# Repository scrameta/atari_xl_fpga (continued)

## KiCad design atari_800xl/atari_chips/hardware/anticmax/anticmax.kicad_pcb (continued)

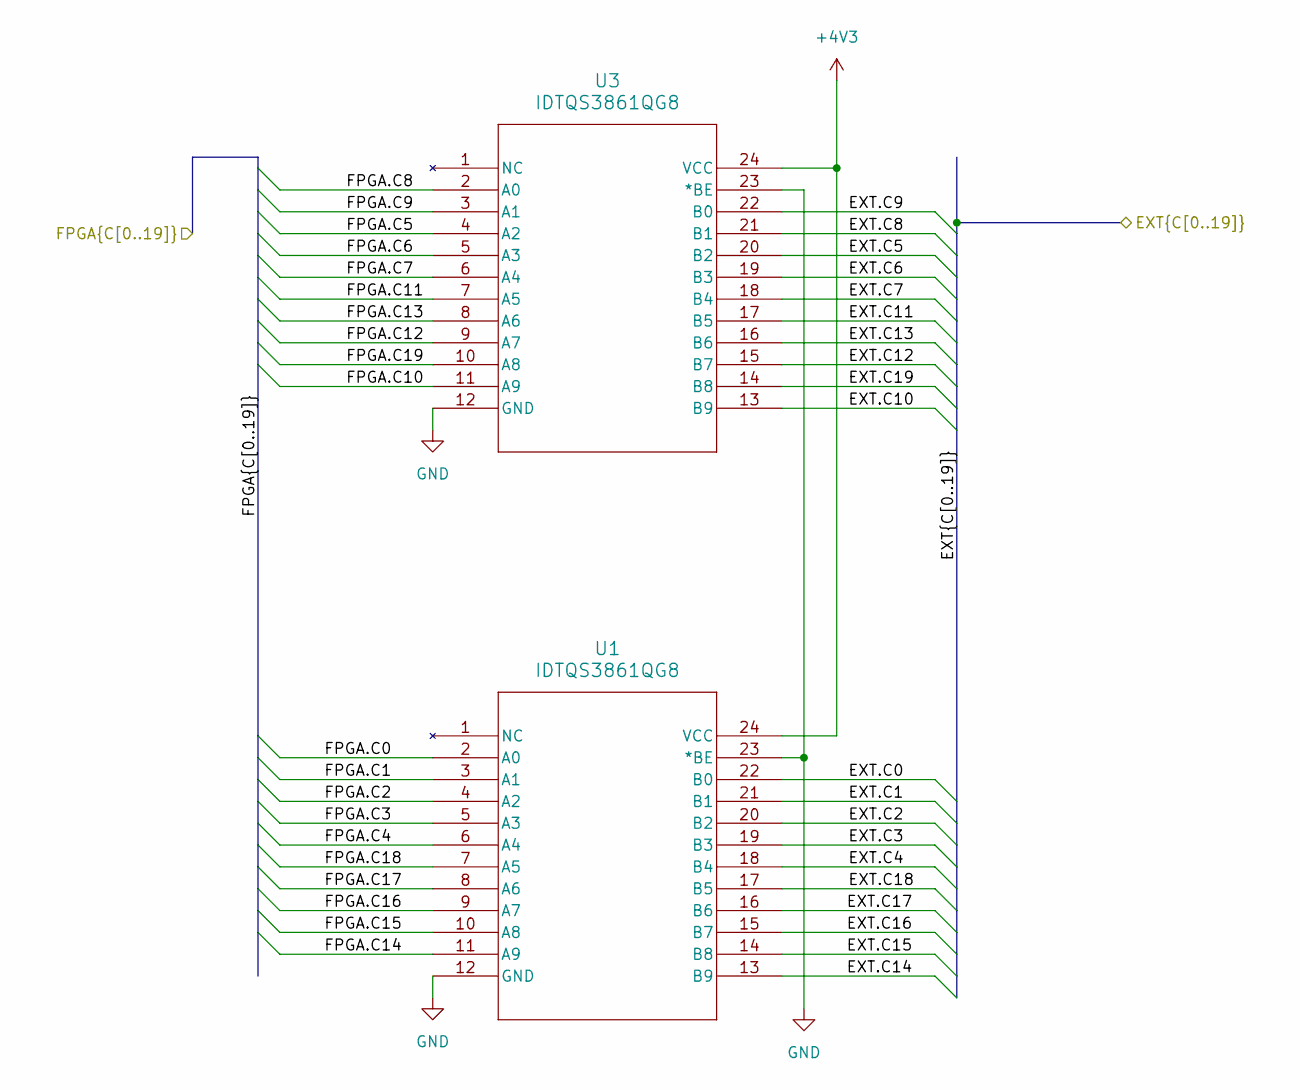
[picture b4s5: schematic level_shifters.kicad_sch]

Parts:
U1, U3: IDTQS3861QG8; QSOP24_SSOP24_REN

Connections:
+4V3: U1.24 (VCC), U3.24 (VCC); also elsewhere on the board
/antic_pins/EXT.C0: U1.22 (B0); also elsewhere on the board
/antic_pins/EXT.C1: U1.21 (B1); also elsewhere on the board
/antic_pins/EXT.C2: U1.20 (B2); also elsewhere on the board
/antic_pins/EXT.C3: U1.19 (B3); also elsewhere on the board
/antic_pins/EXT.C4: U1.18 (B4); also elsewhere on the board
/antic_pins/EXT.C5: U3.20 (B2); also elsewhere on the board
/antic_pins/EXT.C6: U3.19 (B3); also elsewhere on the board
/antic_pins/EXT.C7: U3.18 (B4); also elsewhere on the board
/antic_pins/EXT.C8: U3.21 (B1); also elsewhere on the board
/antic_pins/EXT.C9: U3.22 (B0); also elsewhere on the board
/antic_pins/EXT.C10: U3.13 (B9); also elsewhere on the board
/antic_pins/EXT.C11: U3.17 (B5); also elsewhere on the board
/antic_pins/EXT.C12: U3.15 (B7); also elsewhere on the board
/antic_pins/EXT.C13: U3.16 (B6); also elsewhere on the board
/antic_pins/EXT.C14: U1.13 (B9); also elsewhere on the board
/antic_pins/EXT.C15: U1.14 (B8); also elsewhere on the board
/antic_pins/EXT.C16: U1.15 (B7); also elsewhere on the board
/antic_pins/EXT.C17: U1.16 (B6); also elsewhere on the board
/antic_pins/EXT.C18: U1.17 (B5); also elsewhere on the board
/antic_pins/EXT.C19: U3.14 (B8); also elsewhere on the board
/level shifters/FPGA.C0: U1.2 (A0); also elsewhere on the board
/level shifters/FPGA.C1: U1.3 (A1); also elsewhere on the board
/level shifters/FPGA.C2: U1.4 (A2); also elsewhere on the board
/level shifters/FPGA.C3: U1.5 (A3); also elsewhere on the board
/level shifters/FPGA.C4: U1.6 (A4); also elsewhere on the board
/level shifters/FPGA.C5: U3.4 (A2); also elsewhere on the board
/level shifters/FPGA.C6: U3.5 (A3); also elsewhere on the board
/level shifters/FPGA.C7: U3.6 (A4); also elsewhere on the board
/level shifters/FPGA.C8: U3.2 (A0); also elsewhere on the board
/level shifters/FPGA.C9: U3.3 (A1); also elsewhere on the board
/level shifters/FPGA.C10: U3.11 (A9); also elsewhere on the board
/level shifters/FPGA.C11: U3.7 (A5); also elsewhere on the board
/level shifters/FPGA.C12: U3.9 (A7); also elsewhere on the board
/level shifters/FPGA.C13: U3.8 (A6); also elsewhere on the board
/level shifters/FPGA.C14: U1.11 (A9); also elsewhere on the board
/level shifters/FPGA.C15: U1.10 (A8); also elsewhere on the board
/level shifters/FPGA.C16: U1.9 (A7); also elsewhere on the board
/level shifters/FPGA.C17: U1.8 (A6); also elsewhere on the board
/level shifters/FPGA.C18: U1.7 (A5); also elsewhere on the board
/level shifters/FPGA.C19: U3.10 (A8); also elsewhere on the board
GND: U1.12 (GND), U1.23 (*BE), U3.12 (GND), U3.23 (*BE); also elsewhere on the board

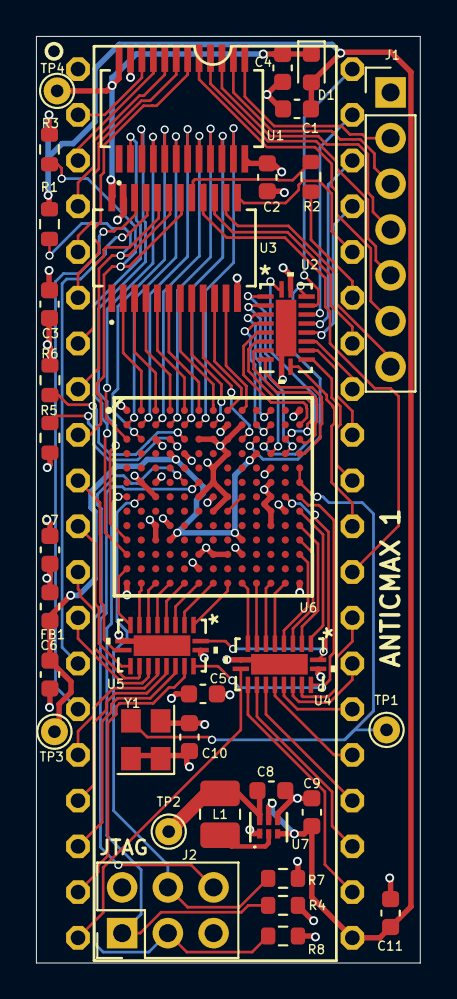
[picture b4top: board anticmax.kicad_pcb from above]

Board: 4 copper layers, 21.3 x 51.5 mm, 37 parts (0 on the bottom side), 107 nets.

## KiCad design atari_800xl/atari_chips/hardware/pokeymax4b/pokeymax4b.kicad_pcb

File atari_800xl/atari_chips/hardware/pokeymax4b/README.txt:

Built and tested as of revision r1474.
Fixed applied from testing that version, but not yet built.

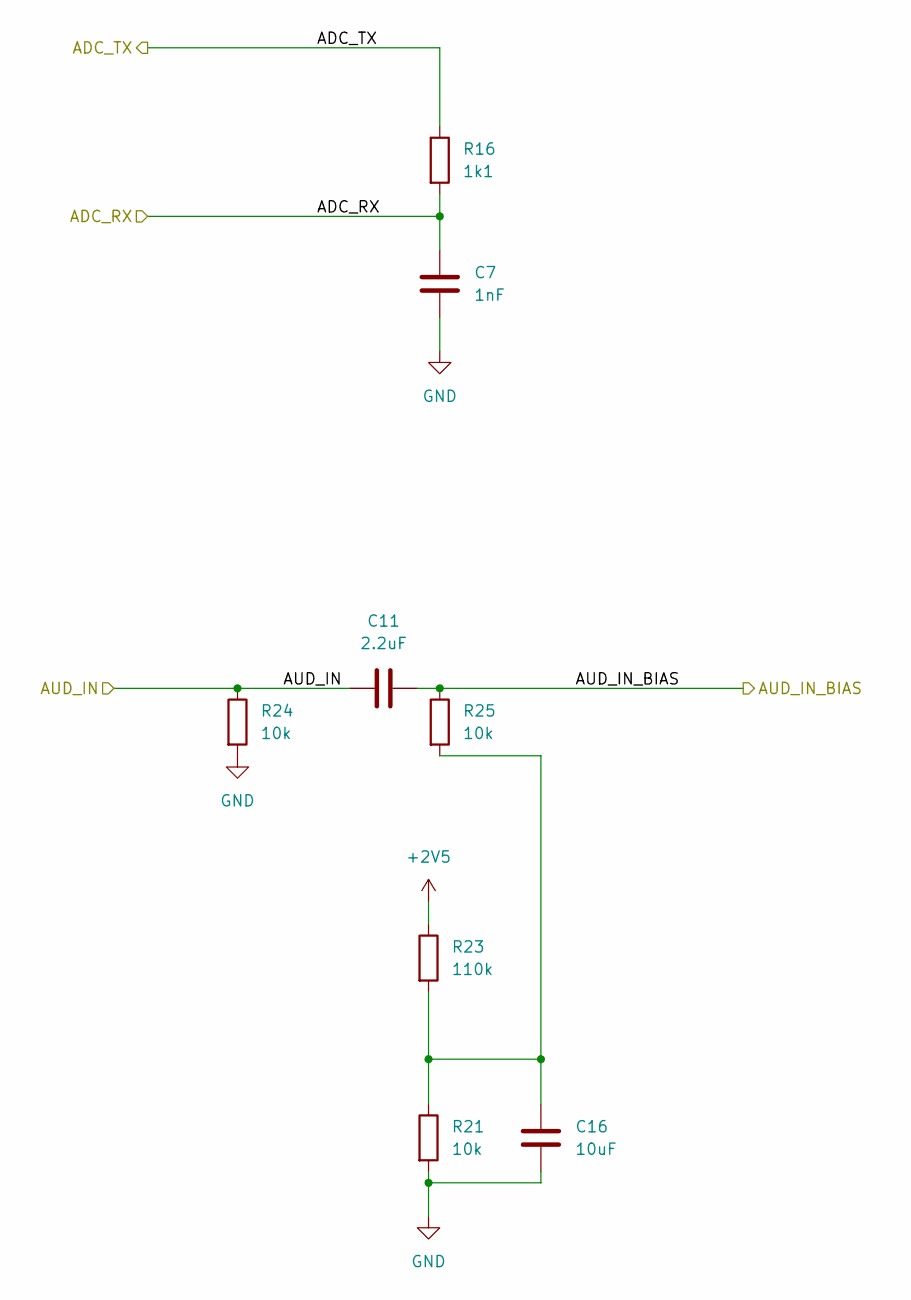
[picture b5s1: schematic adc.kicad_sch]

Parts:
C7: 1nF; C_0603_1608Metric
C11: 2.2uF; C_0603_1608Metric
C16: 10uF; C_0603_1608Metric
R16: 1k1; R_0603_1608Metric
R21, R24, R25: 10k; R_0603_1608Metric
R23: 110k; R_0603_1608Metric

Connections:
+2V5: R23.1; also elsewhere on the board
/ADC/ADC_RX: C7.1, R16.2; also elsewhere on the board
/ADC/ADC_TX: R16.1; also elsewhere on the board
/ADC/AUD_IN: C11.1, R24.1; also elsewhere on the board
/ADC/AUD_IN_BIAS: C11.2, R25.1; also elsewhere on the board
GND: C7.2, C16.1, R21.2, R24.2; also elsewhere on the board
unnamed: C16.2, R21.1, R23.2, R25.2

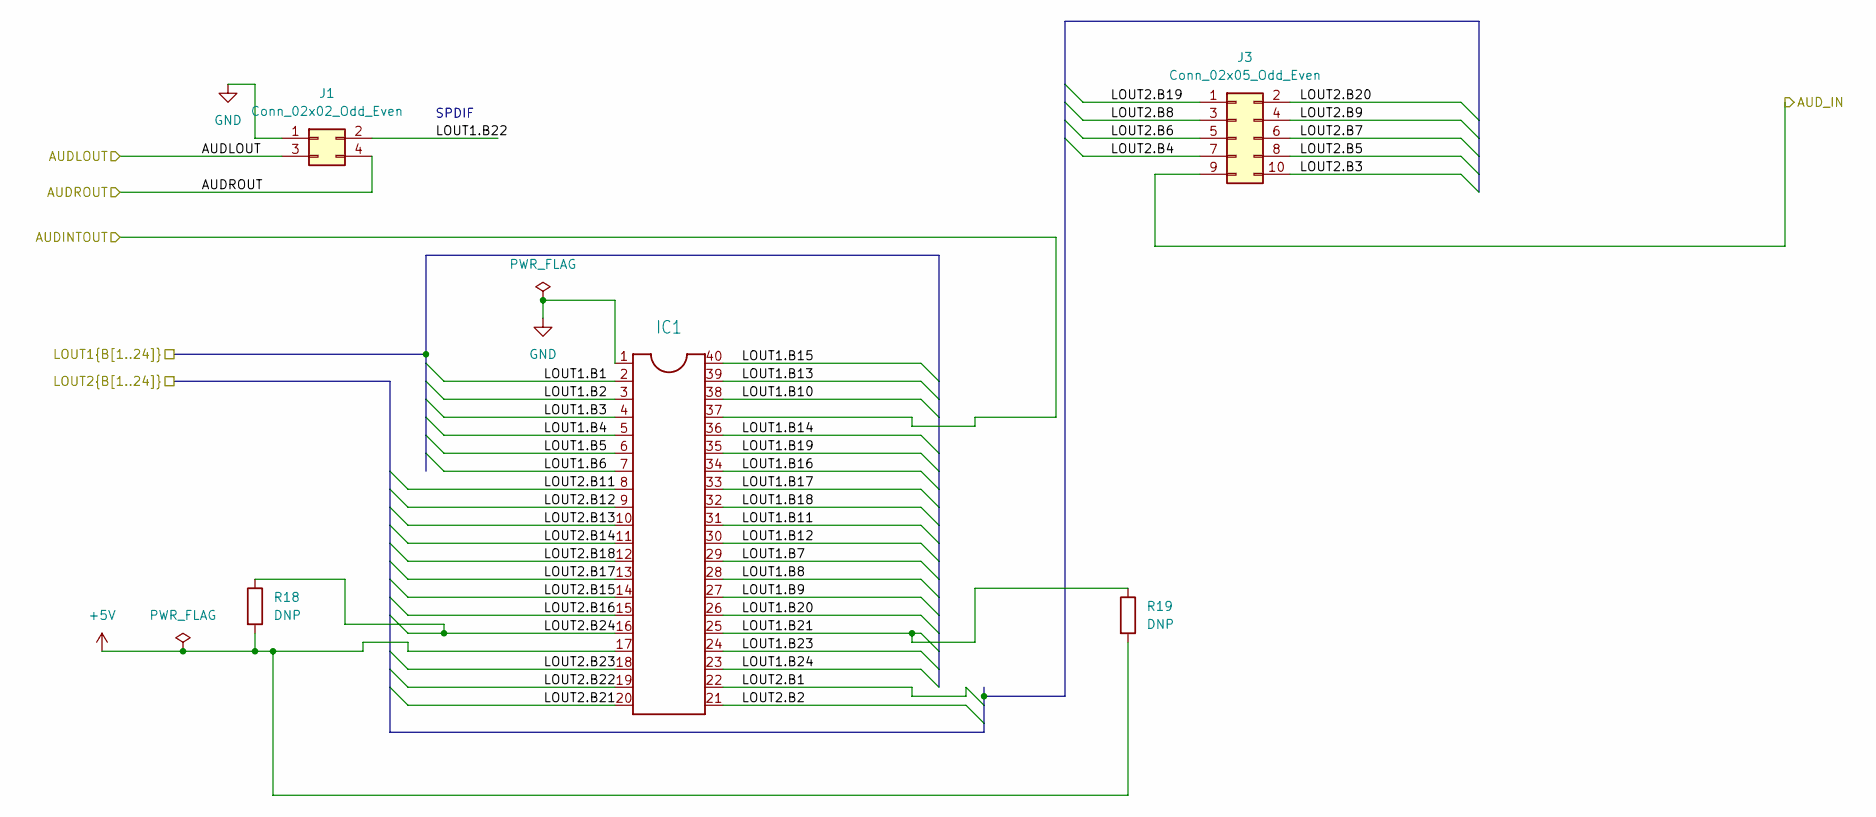
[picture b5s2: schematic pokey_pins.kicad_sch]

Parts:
IC1: DIL40
J1: Conn_02x02_Odd_Even; PinHeader_2x02_P2.54mm_Vertical
J3: Conn_02x05_Odd_Even; PinHeader_2x05_P2.54mm_Vertical
R18, R19: DNP; R_0603_1608Metric

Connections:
+5V: IC1.17, R18.2, R19.2; also elsewhere on the board
/ADC/AUD_IN: J3.9; also elsewhere on the board
/Audio output/AUDLOUT: J1.3; also elsewhere on the board
/Audio output/AUDROUT: J1.4; also elsewhere on the board
/Audio output/AUD_INT_OUT: IC1.37; also elsewhere on the board
/Level shifter/LOUT1.B1: IC1.2; also elsewhere on the board
/Level shifter/LOUT1.B2: IC1.3; also elsewhere on the board
/Level shifter/LOUT1.B3: IC1.4; also elsewhere on the board
/Level shifter/LOUT1.B4: IC1.5; also elsewhere on the board
/Level shifter/LOUT1.B5: IC1.6; also elsewhere on the board
/Level shifter/LOUT1.B6: IC1.7; also elsewhere on the board
/Level shifter/LOUT1.B7: IC1.29; also elsewhere on the board
/Level shifter/LOUT1.B8: IC1.28; also elsewhere on the board
/Level shifter/LOUT1.B9: IC1.27; also elsewhere on the board
/Level shifter/LOUT1.B10: IC1.38; also elsewhere on the board
/Level shifter/LOUT1.B11: IC1.31; also elsewhere on the board
/Level shifter/LOUT1.B12: IC1.30; also elsewhere on the board
/Level shifter/LOUT1.B13: IC1.39; also elsewhere on the board
/Level shifter/LOUT1.B14: IC1.36; also elsewhere on the board
/Level shifter/LOUT1.B15: IC1.40; also elsewhere on the board
/Level shifter/LOUT1.B16: IC1.34; also elsewhere on the board
/Level shifter/LOUT1.B17: IC1.33; also elsewhere on the board
/Level shifter/LOUT1.B18: IC1.32; also elsewhere on the board
/Level shifter/LOUT1.B19: IC1.35; also elsewhere on the board
/Level shifter/LOUT1.B20: IC1.26; also elsewhere on the board
/Level shifter/LOUT1.B21: IC1.25, R19.1; also elsewhere on the board
/Level shifter/LOUT1.B22: J1.2; also elsewhere on the board
/Level shifter/LOUT1.B23: IC1.24; also elsewhere on the board
/Level shifter/LOUT1.B24: IC1.23; also elsewhere on the board
/Level shifter/LOUT2.B1: IC1.22; also elsewhere on the board
/Level shifter/LOUT2.B2: IC1.21; also elsewhere on the board
/Level shifter/LOUT2.B3: J3.10; also elsewhere on the board
/Level shifter/LOUT2.B4: J3.7; also elsewhere on the board
/Level shifter/LOUT2.B5: J3.8; also elsewhere on the board
/Level shifter/LOUT2.B6: J3.5; also elsewhere on the board
/Level shifter/LOUT2.B7: J3.6; also elsewhere on the board
/Level shifter/LOUT2.B8: J3.3; also elsewhere on the board
/Level shifter/LOUT2.B9: J3.4; also elsewhere on the board
/Level shifter/LOUT2.B11: IC1.8; also elsewhere on the board
/Level shifter/LOUT2.B12: IC1.9; also elsewhere on the board
/Level shifter/LOUT2.B13: IC1.10; also elsewhere on the board
/Level shifter/LOUT2.B14: IC1.11; also elsewhere on the board
/Level shifter/LOUT2.B15: IC1.14; also elsewhere on the board
/Level shifter/LOUT2.B16: IC1.15; also elsewhere on the board
/Level shifter/LOUT2.B17: IC1.13; also elsewhere on the board
/Level shifter/LOUT2.B18: IC1.12; also elsewhere on the board
/Level shifter/LOUT2.B19: J3.1; also elsewhere on the board
/Level shifter/LOUT2.B20: J3.2; also elsewhere on the board
/Level shifter/LOUT2.B21: IC1.20; also elsewhere on the board
/Level shifter/LOUT2.B22: IC1.19; also elsewhere on the board
/Level shifter/LOUT2.B23: IC1.18; also elsewhere on the board
/Level shifter/LOUT2.B24: IC1.16, R18.1; also elsewhere on the board
GND: IC1.1, J1.1; also elsewhere on the board

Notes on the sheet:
SPDIF

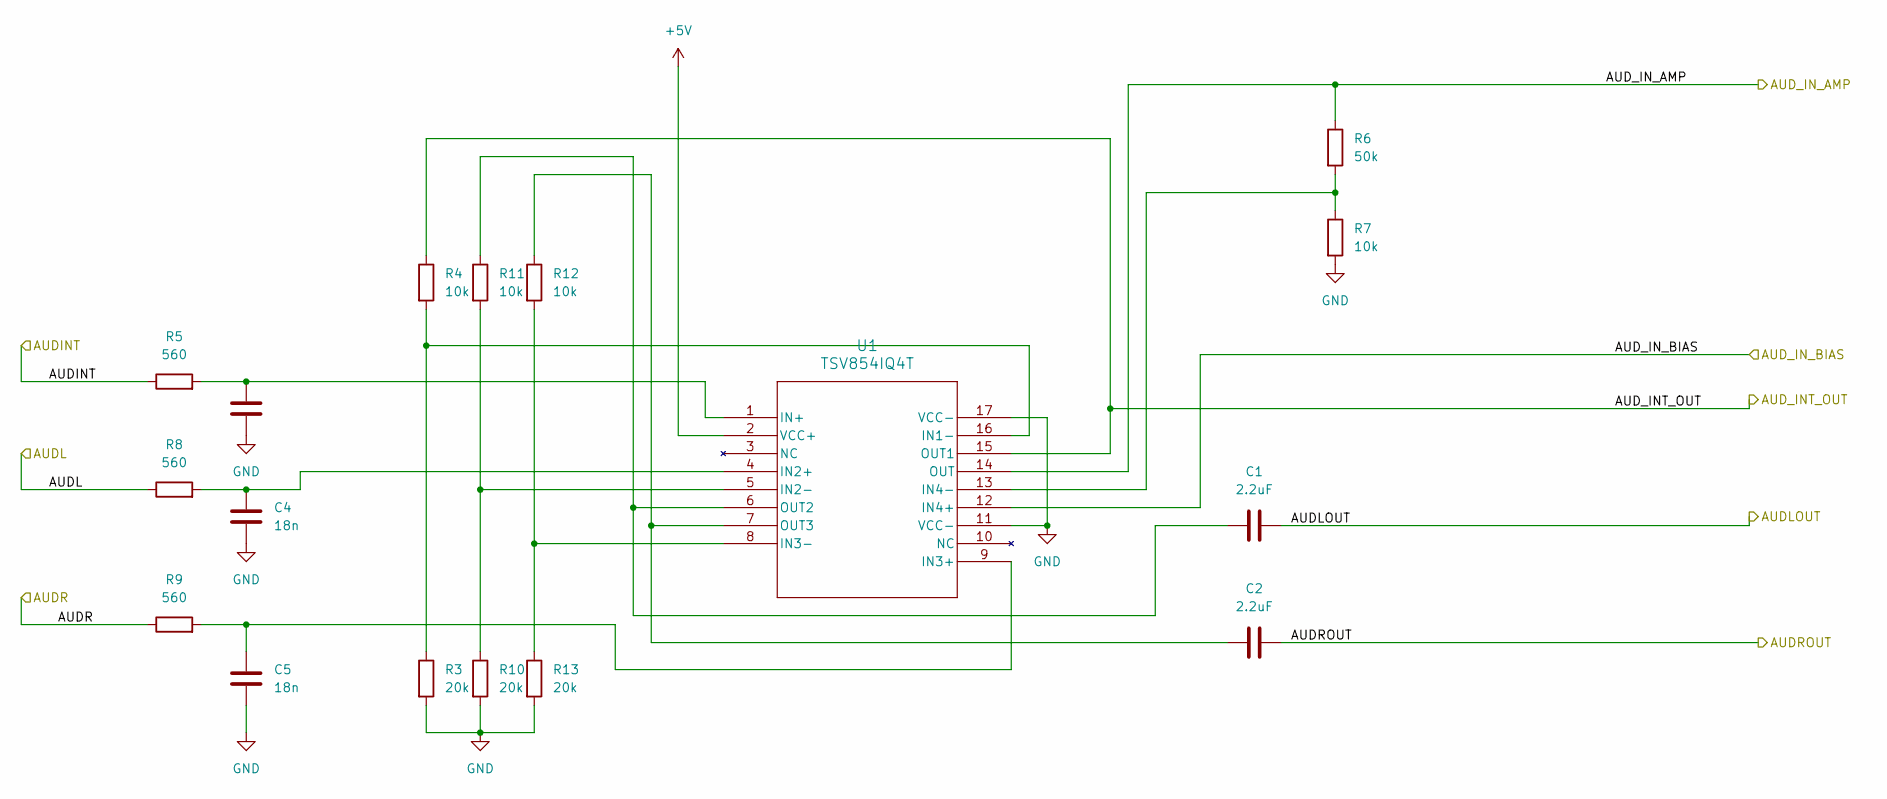
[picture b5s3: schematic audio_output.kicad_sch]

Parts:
C1, C2: 2.2uF; C_0402_1005Metric
C3, C4, C5: 18n; C_0402_1005Metric
R3, R10, R13: 20k; R_0402_1005Metric
R4, R7, R11, R12: 10k; R_0402_1005Metric
R5, R8, R9: 560; R_0402_1005Metric
R6: 50k; R_0402_1005Metric
U1: TSV854IQ4T; QFN16_3X3_STM

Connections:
+5V: U1.2 (VCC+); also elsewhere on the board
/ADC/AUD_IN_BIAS: U1.12 (IN4+); also elsewhere on the board
/Audio output/AUDINT: R5.1; also elsewhere on the board
/Audio output/AUDL: R8.1; also elsewhere on the board
/Audio output/AUDLOUT: C1.2; also elsewhere on the board
/Audio output/AUDR: R9.1; also elsewhere on the board
/Audio output/AUDROUT: C2.2; also elsewhere on the board
/Audio output/AUD_INT_OUT: R4.1, U1.15 (OUT1); also elsewhere on the board
/Audio output/AUD_IN_AMP: R6.1, U1.14 (OUT); also elsewhere on the board
GND: C3.2, C4.2, C5.2, R3.2, R7.2, R10.2, R13.2, U1.11 (VCC-), U1.17 (VCC-); also elsewhere on the board
unnamed: R3.1, R4.2, U1.16 (IN1-)
unnamed: C4.1, R8.2, U1.4 (IN2+)
unnamed: R10.1, R11.2, U1.5 (IN2-)
unnamed: C5.1, R9.2, U1.9 (IN3+)
unnamed: R12.2, R13.1, U1.8 (IN3-)
unnamed: R6.2, R7.1, U1.13 (IN4-)
unnamed: C3.1, R5.2, U1.1 (IN+)
unnamed: C1.1, R11.1, U1.6 (OUT2)
unnamed: C2.1, R12.1, U1.7 (OUT3)

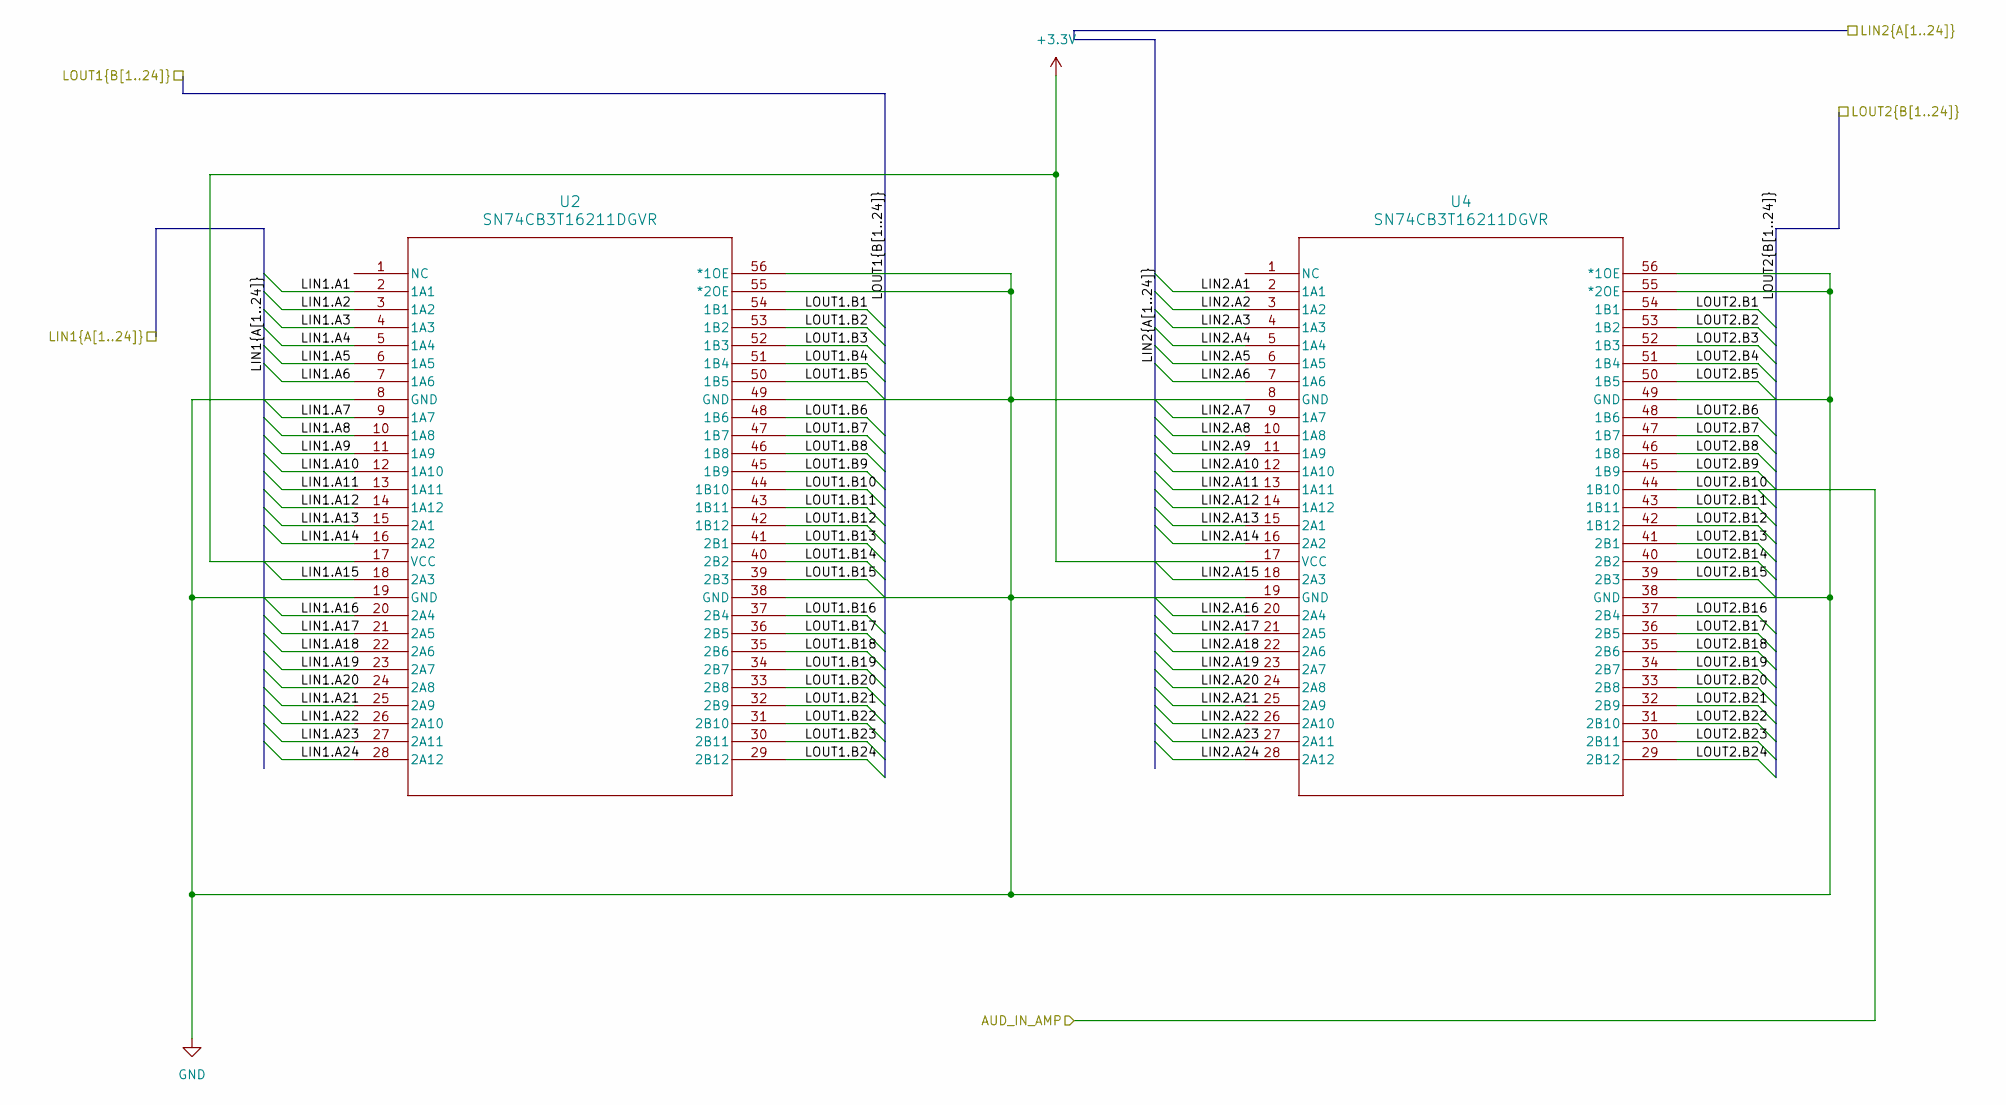
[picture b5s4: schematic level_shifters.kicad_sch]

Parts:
U2, U4: SN74CB3T16211DGVR; DGV56-L

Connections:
+3.3V: U2.17 (VCC), U4.17 (VCC); also elsewhere on the board
/Audio output/AUD_IN_AMP: U4.44 (1B10); also elsewhere on the board
/FPGA/LIN1.A1: U2.2 (1A1); also elsewhere on the board
/FPGA/LIN1.A2: U2.3 (1A2); also elsewhere on the board
/FPGA/LIN1.A3: U2.4 (1A3); also elsewhere on the board
/FPGA/LIN1.A4: U2.5 (1A4); also elsewhere on the board
/FPGA/LIN1.A5: U2.6 (1A5); also elsewhere on the board
/FPGA/LIN1.A6: U2.7 (1A6); also elsewhere on the board
/FPGA/LIN1.A7: U2.9 (1A7); also elsewhere on the board
/FPGA/LIN1.A8: U2.10 (1A8); also elsewhere on the board
/FPGA/LIN1.A9: U2.11 (1A9); also elsewhere on the board
/FPGA/LIN1.A10: U2.12 (1A10); also elsewhere on the board
/FPGA/LIN1.A11: U2.13 (1A11); also elsewhere on the board
/FPGA/LIN1.A12: U2.14 (1A12); also elsewhere on the board
/FPGA/LIN1.A13: U2.15 (2A1); also elsewhere on the board
/FPGA/LIN1.A14: U2.16 (2A2); also elsewhere on the board
/FPGA/LIN1.A15: U2.18 (2A3); also elsewhere on the board
/FPGA/LIN1.A16: U2.20 (2A4); also elsewhere on the board
/FPGA/LIN1.A17: U2.21 (2A5); also elsewhere on the board
/FPGA/LIN1.A18: U2.22 (2A6); also elsewhere on the board
/FPGA/LIN1.A19: U2.23 (2A7); also elsewhere on the board
/FPGA/LIN1.A20: U2.24 (2A8); also elsewhere on the board
/FPGA/LIN1.A21: U2.25 (2A9); also elsewhere on the board
/FPGA/LIN1.A22: U2.26 (2A10); also elsewhere on the board
/FPGA/LIN1.A23: U2.27 (2A11); also elsewhere on the board
/FPGA/LIN1.A24: U2.28 (2A12); also elsewhere on the board
/FPGA/LIN2.A1: U4.2 (1A1); also elsewhere on the board
/FPGA/LIN2.A2: U4.3 (1A2); also elsewhere on the board
/FPGA/LIN2.A3: U4.4 (1A3); also elsewhere on the board
/FPGA/LIN2.A4: U4.5 (1A4); also elsewhere on the board
/FPGA/LIN2.A5: U4.6 (1A5); also elsewhere on the board
/FPGA/LIN2.A6: U4.7 (1A6); also elsewhere on the board
/FPGA/LIN2.A7: U4.9 (1A7); also elsewhere on the board
/FPGA/LIN2.A8: U4.10 (1A8); also elsewhere on the board
/FPGA/LIN2.A9: U4.11 (1A9); also elsewhere on the board
/FPGA/LIN2.A10: U4.12 (1A10); also elsewhere on the board
/FPGA/LIN2.A11: U4.13 (1A11); also elsewhere on the board
/FPGA/LIN2.A12: U4.14 (1A12); also elsewhere on the board
/FPGA/LIN2.A13: U4.15 (2A1); also elsewhere on the board
/FPGA/LIN2.A14: U4.16 (2A2); also elsewhere on the board
/FPGA/LIN2.A15: U4.18 (2A3); also elsewhere on the board
/FPGA/LIN2.A16: U4.20 (2A4); also elsewhere on the board
/FPGA/LIN2.A17: U4.21 (2A5); also elsewhere on the board
/FPGA/LIN2.A18: U4.22 (2A6); also elsewhere on the board
/FPGA/LIN2.A19: U4.23 (2A7); also elsewhere on the board
/FPGA/LIN2.A20: U4.24 (2A8); also elsewhere on the board
/FPGA/LIN2.A21: U4.25 (2A9); also elsewhere on the board
/FPGA/LIN2.A22: U4.26 (2A10); also elsewhere on the board
/FPGA/LIN2.A23: U4.27 (2A11); also elsewhere on the board
/FPGA/LIN2.A24: U4.28 (2A12); also elsewhere on the board
/Level shifter/LOUT1.B1: U2.54 (1B1); also elsewhere on the board
/Level shifter/LOUT1.B2: U2.53 (1B2); also elsewhere on the board
/Level shifter/LOUT1.B3: U2.52 (1B3); also elsewhere on the board
/Level shifter/LOUT1.B4: U2.51 (1B4); also elsewhere on the board
/Level shifter/LOUT1.B5: U2.50 (1B5); also elsewhere on the board
/Level shifter/LOUT1.B6: U2.48 (1B6); also elsewhere on the board
/Level shifter/LOUT1.B7: U2.47 (1B7); also elsewhere on the board
/Level shifter/LOUT1.B8: U2.46 (1B8); also elsewhere on the board
/Level shifter/LOUT1.B9: U2.45 (1B9); also elsewhere on the board
/Level shifter/LOUT1.B10: U2.44 (1B10); also elsewhere on the board
/Level shifter/LOUT1.B11: U2.43 (1B11); also elsewhere on the board
/Level shifter/LOUT1.B12: U2.42 (1B12); also elsewhere on the board
/Level shifter/LOUT1.B13: U2.41 (2B1); also elsewhere on the board
/Level shifter/LOUT1.B14: U2.40 (2B2); also elsewhere on the board
/Level shifter/LOUT1.B15: U2.39 (2B3); also elsewhere on the board
/Level shifter/LOUT1.B16: U2.37 (2B4); also elsewhere on the board
/Level shifter/LOUT1.B17: U2.36 (2B5); also elsewhere on the board
/Level shifter/LOUT1.B18: U2.35 (2B6); also elsewhere on the board
/Level shifter/LOUT1.B19: U2.34 (2B7); also elsewhere on the board
/Level shifter/LOUT1.B20: U2.33 (2B8); also elsewhere on the board
/Level shifter/LOUT1.B21: U2.32 (2B9); also elsewhere on the board
/Level shifter/LOUT1.B22: U2.31 (2B10); also elsewhere on the board
/Level shifter/LOUT1.B23: U2.30 (2B11); also elsewhere on the board
/Level shifter/LOUT1.B24: U2.29 (2B12); also elsewhere on the board
/Level shifter/LOUT2.B1: U4.54 (1B1); also elsewhere on the board
/Level shifter/LOUT2.B2: U4.53 (1B2); also elsewhere on the board
/Level shifter/LOUT2.B3: U4.52 (1B3); also elsewhere on the board
/Level shifter/LOUT2.B4: U4.51 (1B4); also elsewhere on the board
/Level shifter/LOUT2.B5: U4.50 (1B5); also elsewhere on the board
/Level shifter/LOUT2.B6: U4.48 (1B6); also elsewhere on the board
/Level shifter/LOUT2.B7: U4.47 (1B7); also elsewhere on the board
/Level shifter/LOUT2.B8: U4.46 (1B8); also elsewhere on the board
/Level shifter/LOUT2.B9: U4.45 (1B9); also elsewhere on the board
/Level shifter/LOUT2.B11: U4.43 (1B11); also elsewhere on the board
/Level shifter/LOUT2.B12: U4.42 (1B12); also elsewhere on the board
/Level shifter/LOUT2.B13: U4.41 (2B1); also elsewhere on the board
/Level shifter/LOUT2.B14: U4.40 (2B2); also elsewhere on the board
/Level shifter/LOUT2.B15: U4.39 (2B3); also elsewhere on the board
/Level shifter/LOUT2.B16: U4.37 (2B4); also elsewhere on the board
/Level shifter/LOUT2.B17: U4.36 (2B5); also elsewhere on the board
/Level shifter/LOUT2.B18: U4.35 (2B6); also elsewhere on the board
/Level shifter/LOUT2.B19: U4.34 (2B7); also elsewhere on the board
/Level shifter/LOUT2.B20: U4.33 (2B8); also elsewhere on the board
/Level shifter/LOUT2.B21: U4.32 (2B9); also elsewhere on the board
/Level shifter/LOUT2.B22: U4.31 (2B10); also elsewhere on the board
/Level shifter/LOUT2.B23: U4.30 (2B11); also elsewhere on the board
/Level shifter/LOUT2.B24: U4.29 (2B12); also elsewhere on the board
GND: U2.8 (GND), U2.19 (GND), U2.38 (GND), U2.49 (GND), U2.55 (*2OE), U2.56 (*1OE), U4.8 (GND), U4.19 (GND), U4.38 (GND), U4.49 (GND), U4.55 (*2OE), U4.56 (*1OE); also elsewhere on the board

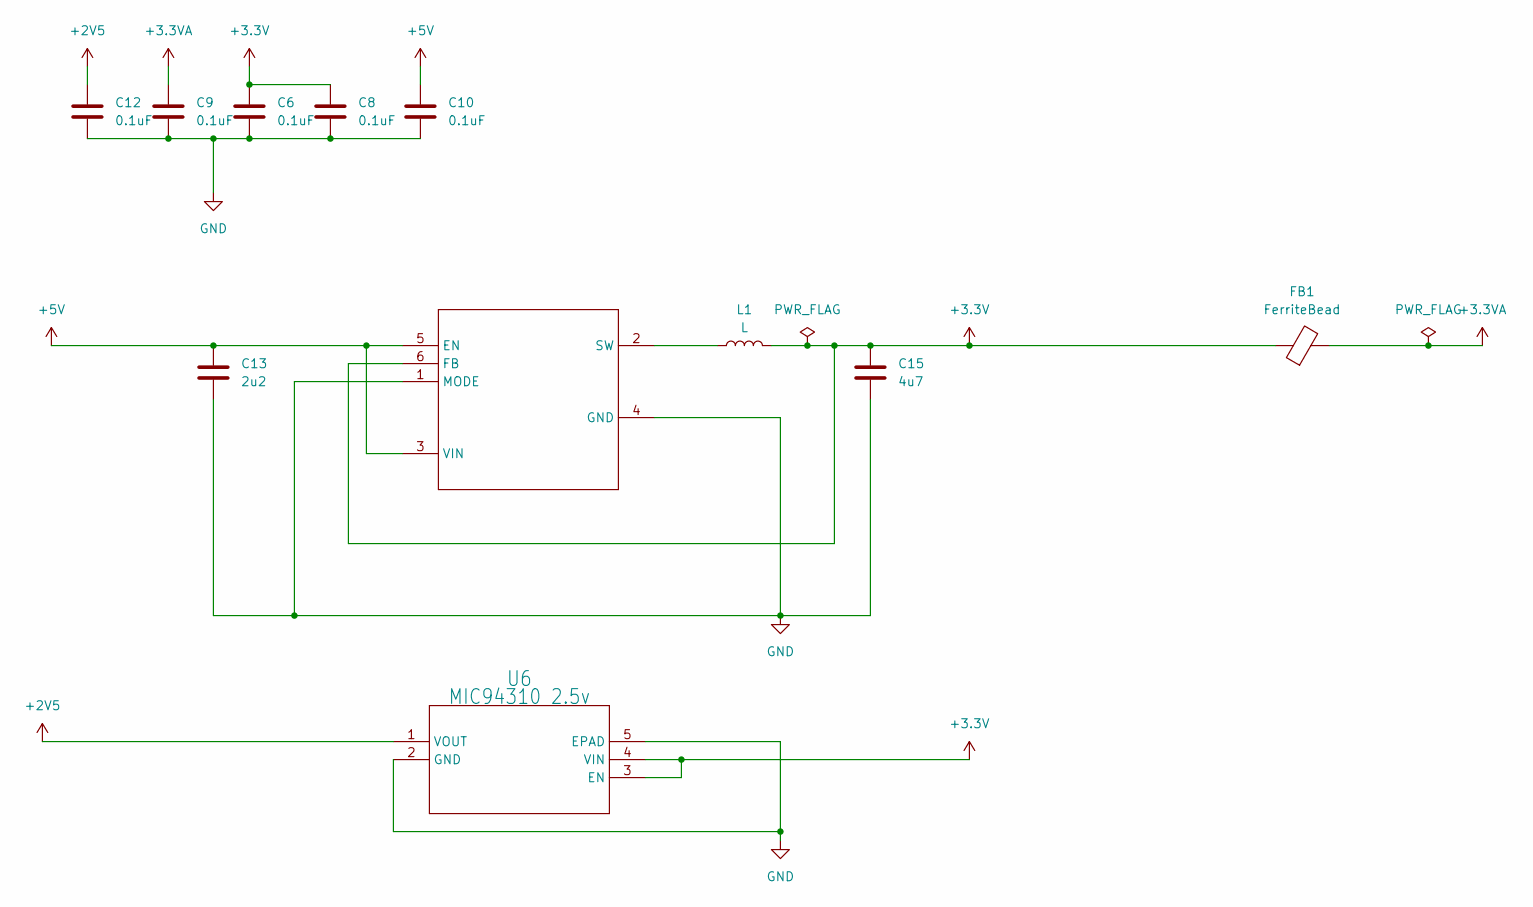
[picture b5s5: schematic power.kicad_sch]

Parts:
C6, C8, C9, C10, C12: 0.1uF; C_0603_1608Metric
C13: 2u2; C_0603_1608Metric
C15: 4u7; C_0603_1608Metric
FB1: FerriteBead; L_0603_1608Metric
L1: L; L_1008_2520Metric_Pad1.43x2.20mm_HandSolder
U5: 3.3v TPS62237; DRY6
U6: MIC94310 2.5v; TDFN4_1P2X1P6_MCH

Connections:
+2V5: C12.1, U6.1 (VOUT); also elsewhere on the board
+3.3V: C6.1, C8.1, C15.1, FB1.1, L1.2, U5.6 (FB), U6.3 (EN), U6.4 (VIN); also elsewhere on the board
+3.3VA: C9.1, FB1.2; also elsewhere on the board
+5V: C10.1, C13.1, U5.3 (VIN), U5.5 (EN); also elsewhere on the board
GND: C6.2, C8.2, C9.2, C10.2, C12.2, C13.2, C15.2, U5.1 (MODE), U5.4 (GND), U6.2 (GND), U6.5 (EPAD); also elsewhere on the board
unnamed: L1.1, U5.2 (SW)

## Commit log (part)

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2020-07-29 Added real 6581 and 8580 filter curves (not switchable yet). Use 16-bit to store them to save rom space
2020-07-29 Allow sid filter selection
2020-07-31 Added notes on the alternative Q setups
2020-08-16 6581/8580 sid mode in config. 6581 is still very basic: fitler curve and no distortion
2020-08-16 Changed to single bit and missed these
2020-08-16 Use correct filter for 8580
2020-08-16 sample/covox cp changes
2020-08-24 The lfsr still needs enabling somehow when the oscillator is stopped, its not clear how this SHOULD work!
2020-09-03 Add external sid and psg clock support, so I can run it in sync with real chips
2020-09-26 Speed up keyboard scanning and fix order - this should fix AKI (but need to test). As for TK2, might be tricky...
2020-09-26 Restrict support
2020-09-26 Store psg volume profile in flash
2020-09-26 Put pokey volume table in flash
2020-09-26 Starvation fix
2020-09-26 PSG at wrong address - typo!!
2020-09-27 Statevariable rom fetch -> generic rom fetch state machine (foundation)
2020-09-28 Add sid wave form to pof+bin after core and update checksum
2020-09-28 SID mixed waveform support from rom
2020-09-28 Use real sid waveforms
2020-09-30 Put 1/Q into rom, with values for 8580 and 6581
2020-10-01 Make pokey mixer request from flash only when needed
2020-10-02 Fix a few errors in the state maching, it was not making requests to flash!
2020-10-02 PSG only requests when needed
2020-10-02 Use real keyboard scan at 1.5MHz i2c clock, for tkii compatibility
2020-10-03 Fix force break - when cleared break no longer forced. Only an issue really when there is no clock, as in certain tape turbo solutions.
2020-10-03 Blank modify, no sid in 02 or 04
2020-10-04 Add more headroom to keyboard scan for TKII (allow int to be later and speed up scan allowing for later int in the cycle)
2020-10-06 IRQ after copying initial data to buffer
2020-10-08 Fix data nibble used for 4-bit mode
2020-10-12 Using a different clock speed for the sigma delta helps with whistling! Need a v2c of hardware really to cut the noise...
2020-10-31 Better handling for TKII, still not 100% but possible to type now!
2020-11-05 SIDMAX v1!
2020-11-06 Add stereo sid. Improve config program display.
2020-11-10 First cut at f distortion. Wrong values and does not fit, but close!
2020-11-14 Setup for 10M16, more changes required but this allow a build
2020-12-16 10M16 flash support
2020-12-19 Updated sigmoid to convient range
2020-12-19 Corrected clock frequency
2020-12-19 f distortion for 6581
2020-12-19 Disable distortion on 8580
2020-12-19 Cut f and distortion precision to make it almost fit in 10M08!
2020-12-19 Rescaled lookup
2020-12-20 Cut area by sharing some parts of envelope. Now JUST fits in v2 with area reduction turned on.
2020-12-20 Typo: wrong lfsr
2020-12-20 Refreshed sid c64 vhd from patch
2020-12-21 Only distort on +ve, now sounding closer...
2020-12-22 SID does not drive the bus when write only or non-decoded registers are read
2021-01-01 Switch to more accurate clock generator, though with jitter. No longer fits on v2, need to find more space!
2021-01-01 Change state machine style so that quartus recognises them, I do not use explicit bit patterns
2021-01-01 Add FAST regs
2021-01-09 Disable, not enough space on v2 full
2021-01-09 Added stereo sid, added 10M04 of the 7800 build
2021-01-09 Fix main envelope and wave timings vs 6581, few scenarios were tested on audiotest board vs a real chip. Add DC offset which is required for sample support. On amplitude modulator in 6581 and on ext 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
2021-01-09 Add basic digifix support (8580D... means 8580 with digifix)
2021-01-09 Change to wrapping burst mode (I do not burst) saves a fair amount of space
2021-01-10 Enable better sid/psg clock support. In order to fit everything into 10M08 had to disable audout2 and change some flash parameters (need verifying)
2021-01-10 This is in fact needed...
2021-01-10 Fixed a few bugs, causing a short final block
2021-01-10 Too small (at least until I remove pokey entirely...)
2021-01-11 Correct maxaddr bug
2021-01-13 Updated version
2021-01-13 Upgraded ip to 20.1.1 versions
2021-01-15 Intel advised that read needed holding loading for wrapping mode to work -> and sure it does. So save this space after all
2021-01-30 Updated to 1.23. Fixed pal reg init. V3: add ps2, spdif and switch to real oscillator. Add more synchronizers to sio.
2021-02-06 Reset ps2 after pll change in case of stuck keys
2021-02-07 Mistification from slingshot, many many many thanks!
2021-02-07 Added new style 32KB roms
2021-02-09 Sync baud fix (was not aligned to enable)
2021-02-09 Added 10M04 versions instead of 10M02 versions
2021-09-01 Test driven SID improvements
2021-09-01 Bug fix
2021-09-01 SIDMAX
2021-09-01 Some new versions added in 123
2021-09-19 Missed from sensitivity list
2021-09-19 Correct v3 sdc file, was effectively entirely missing which broke flash timing. Still needs more work since the sigma delta inputs are effectively not properly constrained.
2021-09-19 Reviewed remaining sdc files
2021-09-19 Allow different settings for with and without sid (for post divide!)
2021-09-19 _ can be in var...
2021-09-21 Two tone reset suppresses the pulse
2021-09-27 Cut 6581 bias, distortion head on basil!
2021-09-29 Moved pokey to a folder
2022-03-18 Synchronous clock length bug fix
2022-03-18 Dev guide 1.22
2022-03-18 Corrected config access value and number of covox registers
2023-02-27 Missed commit, needed to recompute pof file hash
2023-03-27 External clock triggers pulse on both edges. pot resets to 01 instead of 00. cycle exact corrections to audctl.
2023-03-27 Added wide delay line for register delays
2024-03-03 Get prototype working with the latest core
2024-03-03 Merged in non-scalar changes from trunk
2024-03-09 Pull in latest pokey fixes from pokeymax
2024-03-09 Add a pull-up on SD_DETECT and SD_WRITEPROTECT
2024-03-09 Firmware location for small spi flash
2024-03-09 Corrected sdc file, hoping to fix NTSC crashing issue, still failing!
2024-03-09 No longer used now I changed the oscillator
2024-03-10 Trying yet another version of this NTSC mode, that one is still not stable everywhere! Forced a lower fVCO again in pll.m since that seems to help.
2024-03-10 Clearly cartridge d500 on reboot breaks atarimax carts
2024-03-23 Updated to latest zpu code, fixed versions to 38. Added a few missing files. Updated quartus paths.
2024-03-29 Added gerbers for pokeymaxv2b,pokeymaxv3,quad eliminator and sidmax. There are also some brd/sch files though not the latest in all cases
2024-03-29 Seems to be the latest one, I guess it has the spur removal which seems to be a board only setting and schematic is unchanged
2024-03-29 Pure digital 40 pin chip. Needs 5v and gnd wiring on, then can be 6502, antic (I do not have this working yet) or gtia
2024-04-08 Added mountsmd files
2024-04-08 Renumbering left it called pokeymax1
2024-04-09 Try to fit in jlcpcb design rules for 2 layer, larger drills
2024-04-09 Fixed limit, to cover small vias with solder mask
2024-04-17 First cut of pokeymaxv4 core, untested as yet and probably some mistakes. Might also have broken v2/v3, need to test they still build/work
2024-04-23 Added missing lvds
2024-04-28 Mix ADC in
2024-05-11 A few more configs. Note that spdif does not fit on m08 with the full setup.
2024-06-03 Decrease current on FO0, cuts glitches
2024-06-03 Improve phi timing. Try to improve RDY timing.
2024-06-12 Added 10M02 stereo version for v4
2024-06-14 Pull in a cycle fix from trunk
2024-08-31 Sidmax was silent since the pof generation was using a non-existent .cof since it did not detect it as a sid version!
2024-08-31 Update offsets for new quartus versions (TODO: Automate)
2024-08-31 Mixer interface changed slightly
2024-08-31 Had a combinatorial loop, register flash_read. This needs testing on all 04/08/16 combinations!
2024-08-31 pokey1 was missing. Also pokey in sidmax should be the cut down one with keyboard and sio, even the first one!
2024-09-02 Updated ip to quartus v23 version
2024-09-02 Make flash from the svf rather than the pof
2024-09-02 Add other sigmadelta clock
2024-09-02 Split into a block per version. Generate code automatically since I was getting worse and worse. Some clearly overlap. Automatic offsets for patching wave data into CFM. Generate core.bin from svf bl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
2024-09-02 Trivial binary offset search tool
2024-09-02 Move tool build to own script. Added find_offset build.
2024-09-02 Explain where sid offets come from in build.sh
2024-09-05 Pad core.bin out to the actual flash size. Correct version parameter.
2024-09-05 Updated sidcfg. To keep it in sync just use one set of code with a few ifdefs.
2024-09-05 Added sidcfg build
2024-09-05 Apply it to 04 and 08 anyway, consider it safer.
2024-09-05 Putting back to v23 ip. The flash 16 write does not work on old or new versions! Something else is up...
2024-09-05 Some names clash in the hash. Add an extra layer. Also if sidwavedataneeded the value is blank, not zero. So the pof creation fails!
2024-09-05 Fix for 10M16 flash
2024-12-07 Flip sign for spdif. When adc silenced revert back to mixing sio data a bit.
2024-12-08 Only reset serial port on initmode (thanks for detailed bug report to phaeron). This needs testing against real pokey on the harness when I get time, but applying the simple implementation for now.
2024-12-08 Prepare for 1.29 release
2024-12-08 Added another file needed to build
2024-12-10 This is not the right fix. Investing then will commit the right fix.
2024-12-10 Missing comment
2024-12-14 Break out audio detector to own module and improve. Now with zero crossing support.
2024-12-15 Incorrect clock for sio data mixing
2025-06-21 Added some untested kicad designs for pokeymax v4b, pokeymax v4.5, pokeymin v1 and anticmax v1
2025-08-01 Added warning
2025-08-10 Change regulator to a linear one that works with the io pin protection scheme
2025-08-10 Disable dump transistors in fast pot scan mode. When counter is E4 reset allpot_next (it was overwritten because pot_reset_reg is 0).
2025-09-30 VampireV4Standalone core source code, simple port
2025-09-30 Removed bak
2025-10-08 Added paddle mode, needed for 2600daptor - if only I could find it to test it!
2025-10-20 Fix paddle mode, triggers were miswired for years! How did no-one notice?!
2025-11-16 Added pins for pokeymax 4.51 (tested on manually patched 4.5)
2026-02-15 Added dithering with AIs help to reduce idle tones
2026-02-15 Just bash shebang
2026-02-15 Use the same L/R mapping as v4. Added two new components: sync reset and 2nd order dither.
2026-02-15 Default lowpass to on again, think it was off by error
2026-02-15 Disable lowpass again, remembered the filter is explicit for spdif output (where it matters). Make spdif component explicitly have a port for left/right. Get all versions building again (some needed 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
2026-02-16 Turn audio detect back on for v4.5 - silence is golden! Turn on sio data volume too. ADC at 1x is fine though (tested with 150V pk-pk from, iphone into SIO port). Correction of hex data.
2026-03-10 Specified as RW in dev guide
2026-03-19 Less flicker
2026-03-19 Wait after update/verify
2026-03-19 Fix verify/flash success when cancelled
2026-03-24 Preparing for 1.31 which is needed for my mod player!
2026-03-29 Pokeymax v4_53 as produced
2026-05-16 Some test settings crept in
2026-05-24 Forgot to pull in the signed version of covox (to match sample)
2026-05-28 DC blocker gets stuck with small errors. Force min move in the right direction
2026-05-28 Make GTIA keyclick volume closer to original level
2026-05-29 Fix the lost bass
2026-05-29 Share the multiplier in the amplitude modulator
2026-05-30 64KB sample ram on 10M16. Had to use m9k "parity" bit to fit.
2026-05-30 Add sample size of 64K to capability(7)
2026-05-30 No room for 64KB sample memory with FIR filter
2026-05-30 Add a v4 build with 64KB sample ram. Had to drop the fir to fit it, so split the build.
2026-05-30 Get sidmax buiding again by refresing it form the pokeymax changes
2026-05-31 hq_dac needs signed input
2026-06-02 Cut a few registers
2026-06-06 Fix unintentional latch
2026-06-07 Fix for right channel detection logic
2026-06-08 Fix the CPU writes to sample ram
2026-06-08 Fix pm v1 and sidmax builds following sample changes
2026-06-09 Sid routing is using wrong bit
2026-06-14 Move dc blocker to be per unsigned channel. Works better for recording and now everything is signed in priciple with no dc offset for the mixer.
2026-06-14 Only instantiate DC blocker if needed
2026-06-20 Forgot to commit a few files
